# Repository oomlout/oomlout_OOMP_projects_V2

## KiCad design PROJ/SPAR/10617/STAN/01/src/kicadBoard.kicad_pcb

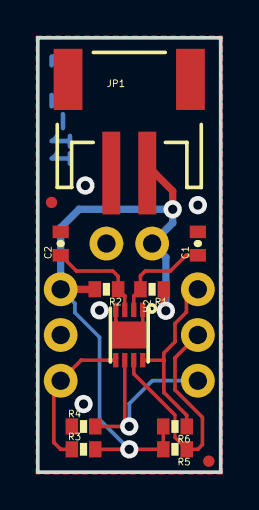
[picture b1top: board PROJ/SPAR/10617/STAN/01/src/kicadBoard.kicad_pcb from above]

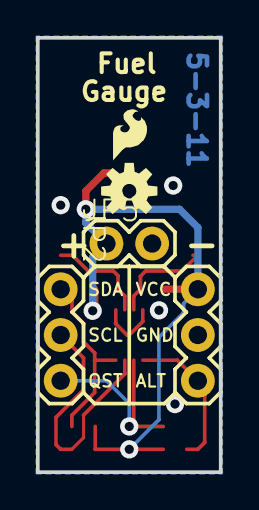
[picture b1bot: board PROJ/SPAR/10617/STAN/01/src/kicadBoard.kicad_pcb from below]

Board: 2 copper layers, 10.2 x 24.1 mm, 17 parts (5 on the bottom side), 8 nets.

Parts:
C1: 1uF; 0402-CAP
C2: 10nF; 0402-CAP
JP1: input; JST-2-SMD
JP2, JP4: 1X03
JP3: LOGO-SFESK; SFE-LOGO-FLAME
JP5: 1X02
JP6, JP7: FIDUCIAL1X2.5; FIDUCIAL-1X2.5
R1: 1k; 0402-RES
R2: 180; 0402-RES
R3, R4, R5, R6: 4.7k; 0402-RES
U2: MAX1704X; TDFN-8
U$1: OSHW-LOGOS; OSHW-LOGO-S

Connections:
ALT: JP4.3, R3.1, U2.5
GND: C1.2, C2.2, JP1.1, JP4.2, JP5.2, R4.1, U2.1, U2.4, U2.EP
unnamed: C1.1, R1.2, U2.2
QST: JP2.3, R4.2, U2.6
SCL: JP2.2, R5.1, U2.7
SDA: JP2.1, R6.1, U2.8
VCC: JP1.2, JP4.1, JP5.1, R1.1, R2.2, R3.2, R5.2, R6.2
VDD: C2.1, R2.1, U2.3

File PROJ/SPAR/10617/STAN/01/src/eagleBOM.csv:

"Part";"Value";"Device";"Package";"Description";"";
"C1";"1uF";"CAP0402-CAP";"0402-CAP";"Capacitor";"";
"C2";"10nF";"CAP0402-CAP";"0402-CAP";"Capacitor";"";
"JP1";"input";"M02-JST-2MM-SMT";"JST-2-SMD";"Header 2";"";
"JP2";"";"M03PTH";"1X03";"Header 3";"";
"JP3";"LOGO-SFESK";"LOGO-SFESK";"SFE-LOGO-FLAME";"Spark Fun Electronics PCB Logo";"";
"JP4";"";"M03PTH";"1X03";"Header 3";"";
"JP5";"";"M02PTH";"1X02";"Header 2";"";
"JP6";"FIDUCIAL1X2.5";"FIDUCIAL1X2.5";"FIDUCIAL-1X2.5";"Fiducial Alignment Points";"";
"JP7";"FIDUCIAL1X2.5";"FIDUCIAL1X2.5";"FIDUCIAL-1X2.5";"Fiducial Alignment Points";"";
"R1";"1k";"RESISTOR0402-RES";"0402-RES";"Resistor";"";
"R2";"180";"RESISTOR0402-RES";"0402-RES";"Resistor";"";
"R3";"4.7k";"RESISTOR0402-RES";"0402-RES";"Resistor";"";
"R4";"4.7k";"RESISTOR0402-RES";"0402-RES";"Resistor";"";
"R5";"4.7k";"RESISTOR0402-RES";"0402-RES";"Resistor";"";
"R6";"4.7k";"RESISTOR0402-RES";"0402-RES";"Resistor";"";
"U$1";"OSHW-LOGOS";"OSHW-LOGOS";"OSHW-LOGO-S";"Open Source Hardware Logo This logo indicates the piece of hardware it is found on incorporates a OSHW license and/or adheres to the definition of open source hardware found here: http://freedomdefined.org/OSHW";"";
"U2";"MAX1704X";"MAX1704X";"TDFN-8";"MAX17043/MAX17044: Battery Fuel Guage (43 is 1cell, 44 is 2cell)";"";

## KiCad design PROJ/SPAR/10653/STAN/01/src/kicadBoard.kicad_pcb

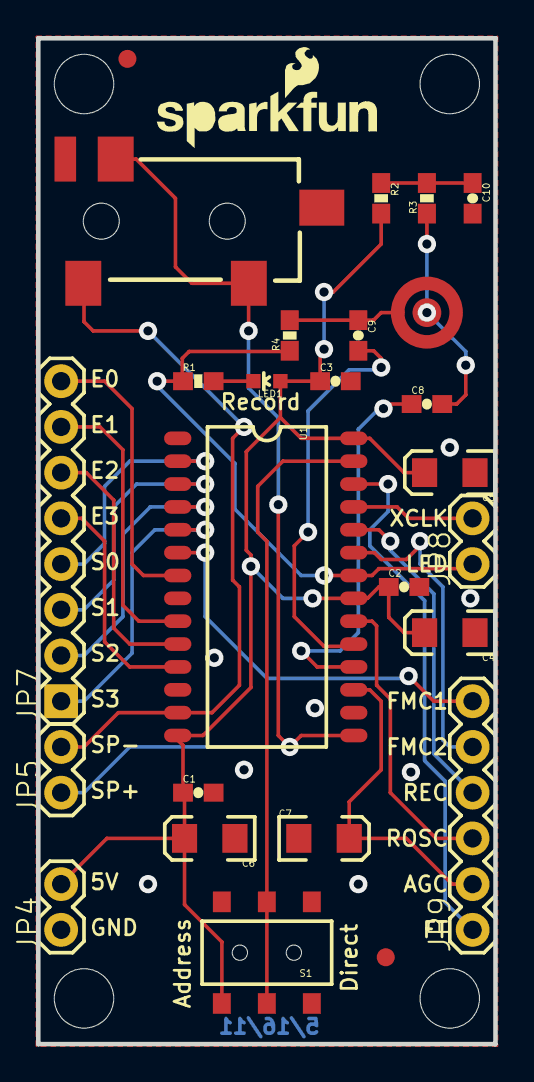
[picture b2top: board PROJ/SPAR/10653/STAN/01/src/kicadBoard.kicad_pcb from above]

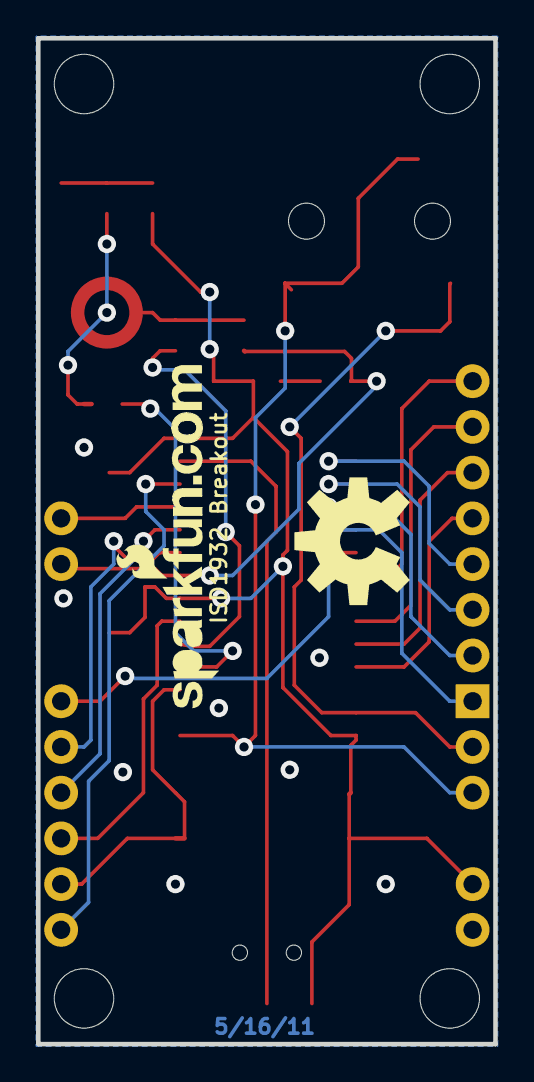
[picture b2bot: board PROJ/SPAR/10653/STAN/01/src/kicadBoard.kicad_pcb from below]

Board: 2 copper layers, 25.4 x 55.9 mm, 35 parts (2 on the bottom side), 27 nets.

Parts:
C1, C2, C3, C8, C9: 0.1uF; 0603-CAP
C4, C5, C6, C7: 10uF; EIA3216
C10: 4.7uF; 0603-CAP
JP1: LOGO-SFENEW; SFE-NEW-WEBLOGO
JP2, JP3: FIDUCIAL1X2; FIDUCIAL-1X2
JP4, JP5, JP8: 1X02
JP6, JP10, JP11, JP12: STAND-OFF
JP7: 1X08
JP9: 1X06
JP13: LOGO-SFENW2; SFE-NEW-WEB
LED1: Red; LED-0603
R1: 1k; 0603-RES
R2, R3, R4: 4.7k; 0603-RES
S1: AYZ0202
U1: ISD1900ISD1932; SO-28W
U2: MICELECTRET_SMD; MIC_ELECTRET_SMD
U3: AUDIO-JACK2SMD; AUDIO-JACK-3.5MM-SMD
U$10: CREATIVE_COMMONS
U$13: SFE-LOGO-FLAME
U$14: OSHW-LOGOL; OSHW-LOGO-L

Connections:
5V: C1.1, C2.1, C3.1, C4.A, C5.A, C6.A, JP4.2, LED1.A, R2.2, S1.3, U1.14, U1.21, U1.28
AGC: C7.A, JP9.2, U1.17
E0: JP7.8, U1.7
E1: JP7.7, U1.9
E2: JP7.6, U1.10
E3: JP7.5, U1.11
FMC1: JP9.6, U1.6
FMC2: JP9.5, U1.23
FT: JP9.1, U1.26
GND: C1.2, C2.2, C3.2, C4.C, C5.C, C6.C, C7.C, C10.2, JP4.1, S1.1, U1.1, U1.8, U1.12, U1.16
LED: JP8.1, R1.1, R4.1, U1.22
MIC+: C8.1, U1.18
MIC-: C9.2, U1.19
MODE: S1.2, U1.27
unnamed: LED1.C, R1.2
unnamed: C8.2, R3.1, U2.1
unnamed: C9.1, R4.2, U2.2
unnamed: C10.1, R2.1, R3.2
REC: JP9.4, U1.24
ROSC: JP9.3, U1.20
S0: JP7.4, U1.2
S1: JP7.3, U1.3
S2: JP7.2, U1.4
S3: JP7.1, U1.5
SP+: JP5.1, U1.15, U3.RING, U3.TIP
SP-: JP5.2, U1.13, U3.SLEEVE
XCLK: JP8.2, U1.25

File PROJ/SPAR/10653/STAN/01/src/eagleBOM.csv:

"Part";"Value";"Device";"Package";"Description";"";
"C1";"0.1uF";"CAP0603-CAP";"0603-CAP";"Capacitor";"";
"C2";"0.1uF";"CAP0603-CAP";"0603-CAP";"Capacitor";"";
"C3";"0.1uF";"CAP0603-CAP";"0603-CAP";"Capacitor";"";
"C4";"10uF";"CAP_POL1206";"EIA3216";"Capacitor Polarized";"";
"C5";"10uF";"CAP_POL1206";"EIA3216";"Capacitor Polarized";"";
"C6";"10uF";"CAP_POL1206";"EIA3216";"Capacitor Polarized";"";
"C7";"10uF";"CAP_POL1206";"EIA3216";"Capacitor Polarized";"";
"C8";"0.1uF";"CAP0603-CAP";"0603-CAP";"Capacitor";"";
"C9";"0.1uF";"CAP0603-CAP";"0603-CAP";"Capacitor";"";
"C10";"4.7uF";"CAP0603-CAP";"0603-CAP";"Capacitor";"";
"JP1";"LOGO-SFENEW";"LOGO-SFENEW";"SFE-NEW-WEBLOGO";"Spark Fun Electronics PCB Logo";"";
"JP2";"FIDUCIAL1X2";"FIDUCIAL1X2";"FIDUCIAL-1X2";"Fiducial Alignment Points";"";
"JP3";"FIDUCIAL1X2";"FIDUCIAL1X2";"FIDUCIAL-1X2";"Fiducial Alignment Points";"";
"JP4";"";"M02PTH";"1X02";"Header 2";"";
"JP5";"";"M02PTH";"1X02";"Header 2";"";
"JP6";"STAND-OFF";"STAND-OFF";"STAND-OFF";"Stand Off";"";
"JP7";"";"M08";"1X08";"Header 8";"";
"JP8";"";"M02PTH";"1X02";"Header 2";"";
"JP9";"";"M06SIP";"1X06";"Header 6";"";
"JP10";"STAND-OFF";"STAND-OFF";"STAND-OFF";"Stand Off";"";
"JP11";"STAND-OFF";"STAND-OFF";"STAND-OFF";"Stand Off";"";
"JP12";"STAND-OFF";"STAND-OFF";"STAND-OFF";"Stand Off";"";
"JP13";"LOGO-SFENW2";"LOGO-SFENW2";"SFE-NEW-WEB";"Spark Fun Electronics PCB Logo";"";
"LED1";"Red";"LED0603";"LED-0603";"LEDs";"";
"R1";"1k";"RESISTOR0603-RES";"0603-RES";"Resistor";"";
"R2";"4.7k";"RESISTOR0603-RES";"0603-RES";"Resistor";"";
"R3";"4.7k";"RESISTOR0603-RES";"0603-RES";"Resistor";"";
"R4";"4.7k";"RESISTOR0603-RES";"0603-RES";"Resistor";"";
"S1";"";"SWITCH-SPSTSMD";"AYZ0202";"SPST Switch";"";
"U$10";"CREATIVE_COMMONS";"CREATIVE_COMMONS";"CREATIVE_COMMONS";"";"";
"U$14";"OSHW-LOGOL";"OSHW-LOGOL";"OSHW-LOGO-L";"Open Source Hardware Logo This logo indicates the piece of hardware it is found on incorporates a OSHW license and/or adheres to the definition of open source hardware found here: http://freedomdefined.org/OSHW";"";
"U1";"ISD1900ISD1932";"ISD1900ISD1932";"SO-28W";"";"";
"U2";"MICELECTRET_SMD";"MICELECTRET_SMD";"MIC_ELECTRET_SMD";"Microphone";"";
"U3";"AUDIO-JACK2SMD";"AUDIO-JACK2SMD";"AUDIO-JACK-3.5MM-SMD";"";"";

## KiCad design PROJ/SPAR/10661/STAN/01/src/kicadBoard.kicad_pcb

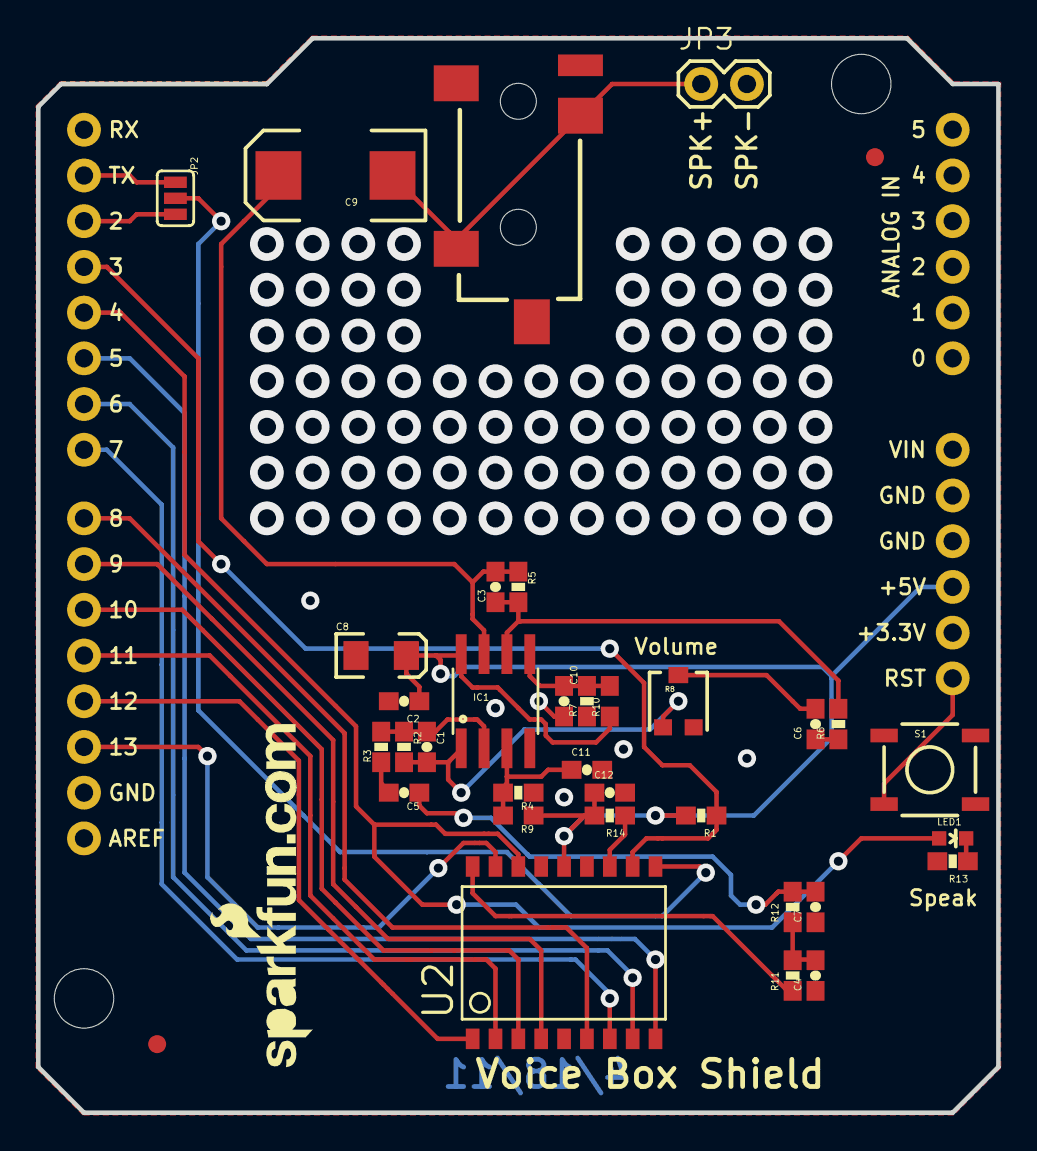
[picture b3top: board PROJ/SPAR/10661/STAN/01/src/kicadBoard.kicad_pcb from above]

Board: 2 copper layers, 53.3 x 59.7 mm, 37 parts (0 on the bottom side), 32 nets.

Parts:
C1, C3: 100pF; 0603-CAP
C2, C12: 0.1uF; 0603-CAP
C4, C7: 10 nF; 0603-CAP
C5, C6, C10, C11: 1uF; 0603-CAP
C8: 10uF; EIA3216
C9: 100 uF; EIA7343
IC1: OPAMP-DUALU; SO08
JP1: LOGO-SFENEW; SFE-NEW-WEBLOGO
JP2: JUMPER-32-3; SJ_3_PASTE2&3
JP3: Audio Header; 1X02
JP4, JP5: FIDUCIAL1X2; FIDUCIAL-1X2
JP6: 3.5mm SMD Audio Jack; AUDIO-JACK-3.5MM-SMD
LED1: Green; LED-0603
R1, R14: 10k; 0603-RES
R2, R5: 100K; 0603-RES
R3, R4, R6, R7: 10K; 0603-RES
R8: 10K Trimpot; TRIMPOT-3MM
R9, R10: 10K; 0603
R11, R12: 28k; 0603-RES
R13: 330; 0603-RES
S1: Reset Switch; TACTILE_SWITCH_SMD
U1: ARDUINO_SHIELDLABEL; DUEMILANOVE_SHIELD
U2: SPEAKJETSMD_WIDE; SO-18W

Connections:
AUDIO: C9.C, JP3.1, JP6.RING, JP6.TIP
D-TX: JP2.3, U1.D2
E0: U1.D5, U2.9
E1: U1.D6, U2.8
E2: U1.D7, U2.7
E3: U1.D8, U2.6
E4: U1.D9, U2.4
E5: U1.D10, U2.3
E6: U1.D11, U2.2
E7: U1.D12, U2.1
GND: C2.2, C4.1, C7.1, C8.C, C10.2, C11.2, C12.2, IC1.4, JP3.2, JP6.SLEEVE, R4.1, R7.1, R8.3, R13.2, S1.1, U1.GND@0, U1.GND@1, U1.GND@2, U2.5, U2.13
IN1: C5.2, R3.1
unnamed: JP2.2, U2.10
unnamed: C1.1, IC1.2, R2.1, R3.2
unnamed: C6.1, R6.1
unnamed: C6.2, R8.2
unnamed: C3.1, IC1.6, R5.2, R6.2
unnamed: C10.1, IC1.5, R7.2, R10.2
unnamed: C11.1, IC1.3, R4.2, R9.2
unnamed: C4.2, R11.2, R12.1
unnamed: C5.1, C7.2, R12.2
unnamed: LED1.C, R13.1
unnamed: R14.1, U2.12
OUT1: C1.2, IC1.1, R2.2, R8.1
RDY: U1.D13, U2.17
RESET: S1.3, U1.RES
RST: R1.1, U1.D3, U2.11
SPK: LED1.A, U1.D4, U2.16
SPK+: C3.2, C9.A, IC1.7, R5.1
TX: JP2.1, U1.TX
VCC: C2.1, C8.A, C12.1, IC1.8, R1.2, R9.1, R10.1, R14.2, U1.5V, U2.14
V_OUT: R11.1, U2.18

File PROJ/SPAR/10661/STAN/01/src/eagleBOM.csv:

"Part";"Value";"Device";"Package";"Description";"";
"C1";"100pF";"CAP0603-CAP";"0603-CAP";"Capacitor";"";
"C2";"0.1uF";"CAP0603-CAP";"0603-CAP";"Capacitor";"";
"C3";"100pF";"CAP0603-CAP";"0603-CAP";"Capacitor";"";
"C4";"10 nF";"CAP0603-CAP";"0603-CAP";"Capacitor";"";
"C5";"1uF";"CAP0603-CAP";"0603-CAP";"Capacitor";"";
"C6";"1uF";"CAP0603-CAP";"0603-CAP";"Capacitor";"";
"C7";"10 nF";"CAP0603-CAP";"0603-CAP";"Capacitor";"";
"C8";"10uF";"CAP_POL1206";"EIA3216";"Capacitor Polarized";"";
"C9";"100 uF";"CAP_POL7343";"EIA7343";"Capacitor Polarized";"";
"C10";"1uF";"CAP0603-CAP";"0603-CAP";"Capacitor";"";
"C11";"1uF";"CAP0603-CAP";"0603-CAP";"Capacitor";"";
"C12";"0.1uF";"CAP0603-CAP";"0603-CAP";"Capacitor";"";
"IC1";"OPAMP-DUALU";"OPAMP-DUALU";"SO08";"Operational Amplifier";"";
"JP1";"LOGO-SFENEW";"LOGO-SFENEW";"SFE-NEW-WEBLOGO";"Spark Fun Electronics PCB Logo";"";
"JP2";"JUMPER-32-3";"JUMPER-32-3";"SJ_3_PASTE2&3";"";"";
"JP3";"Audio Header";"M02PTH";"1X02";"Header 2";"";
"JP4";"FIDUCIAL1X2";"FIDUCIAL1X2";"FIDUCIAL-1X2";"Fiducial Alignment Points";"";
"JP5";"FIDUCIAL1X2";"FIDUCIAL1X2";"FIDUCIAL-1X2";"Fiducial Alignment Points";"";
"JP6";"3.5mm SMD Audio Jack";"AUDIO-JACKSMD2";"AUDIO-JACK-3.5MM-SMD";"3.5mm Audio Jack";"";
"LED1";"Green";"LED0603";"LED-0603";"LEDs";"";
"R1";"10k";"RESISTOR0603-RES";"0603-RES";"Resistor";"";
"R2";"100K";"RESISTOR0603-RES";"0603-RES";"Resistor";"";
"R3";"10K";"RESISTOR0603-RES";"0603-RES";"Resistor";"";
"R4";"10K";"RESISTOR0603-RES";"0603-RES";"Resistor";"";
"R5";"100K";"RESISTOR0603-RES";"0603-RES";"Resistor";"";
"R6";"10K";"RESISTOR0603-RES";"0603-RES";"Resistor";"";
"R7";"10K";"RESISTOR0603-RES";"0603-RES";"Resistor";"";
"R8";"10K Trimpot";"TRIMPOTSMD";"TRIMPOT-3MM";"";"";
"R9";"10K";"RESISTOR0603";"0603";"Resistor";"";
"R10";"10K";"RESISTOR0603";"0603";"Resistor";"";
"R11";"28k";"RESISTOR0603-RES";"0603-RES";"Resistor";"";
"R12";"28k";"RESISTOR0603-RES";"0603-RES";"Resistor";"";
"R13";"330";"RESISTOR0603-RES";"0603-RES";"Resistor";"";
"R14";"10k";"RESISTOR0603-RES";"0603-RES";"Resistor";"";
"S1";"Reset Switch";"SWITCH-MOMENTARY-2SMD";"TACTILE_SWITCH_SMD";"";"";
"U1";"ARDUINO_SHIELDLABEL";"ARDUINO_SHIELDLABEL";"DUEMILANOVE_SHIELD";"";"";
"U2";"SPEAKJETSMD_WIDE";"SPEAKJETSMD_WIDE";"SO-18W";"";"";

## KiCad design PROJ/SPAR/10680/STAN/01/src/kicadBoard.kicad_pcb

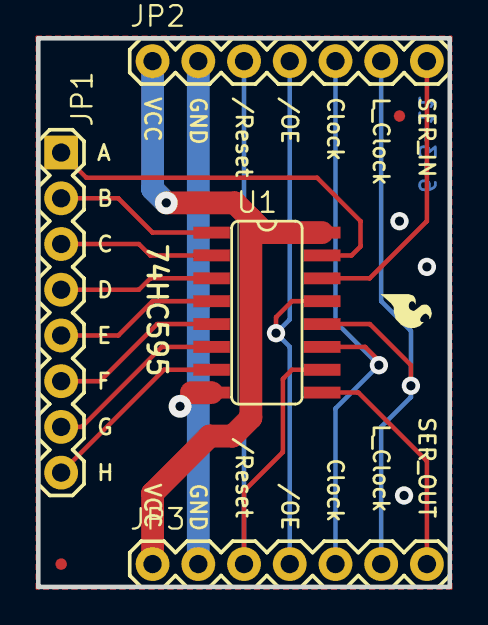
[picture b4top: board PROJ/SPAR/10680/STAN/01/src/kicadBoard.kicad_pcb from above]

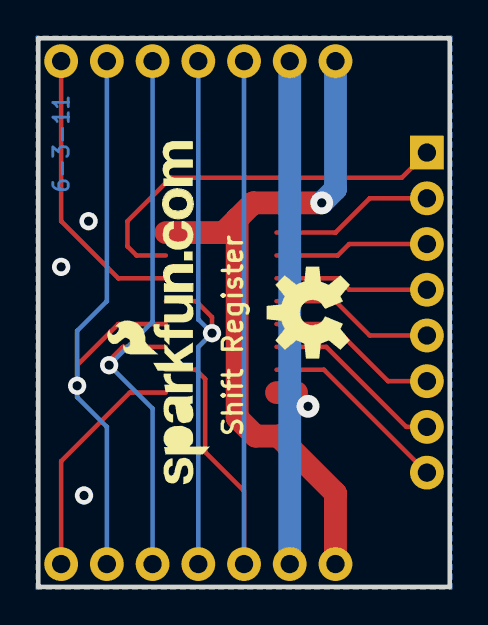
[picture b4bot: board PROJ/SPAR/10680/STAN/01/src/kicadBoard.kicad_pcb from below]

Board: 2 copper layers, 22.9 x 30.5 mm, 10 parts (2 on the bottom side), 16 nets.

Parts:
JP1: 1X08
JP2, JP3: 1X07
JP4: LOGO-SFENEW; SFE-NEW-WEBLOGO
JP5: LOGO-SFESK; SFE-LOGO-FLAME
JP6, JP7: FIDUCIAL1X2.5; FIDUCIAL-1X2.5
U1: 74LS595D; SO16
U$1: OSHW-LOGOM; OSHW-LOGO-M
U$2: CREATIVE_COMMONS

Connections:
/OUTPUT_ENABLE: JP2.4, JP3.4, U1.13
/RESET: JP2.3, JP3.3, U1.10
CLOCK: JP2.5, JP3.5, U1.11
GND: JP2.2, JP3.2, U1.8
LATCH_CLOCK: JP2.6, JP3.6, U1.12
unnamed: JP1.1, U1.15
unnamed: JP1.2, U1.1
unnamed: JP1.3, U1.2
unnamed: JP1.4, U1.3
unnamed: JP1.5, U1.4
unnamed: JP1.6, U1.5
unnamed: JP1.7, U1.6
unnamed: JP1.8, U1.7
SERIAL_IN: JP2.7, U1.14
SERIAL_OUT: JP3.7, U1.9
VCC: JP2.1, JP3.1, U1.16

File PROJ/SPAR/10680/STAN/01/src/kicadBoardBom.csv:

"Id";"Designator";"Package";"Quantity";"Designation";"Supplier and ref";
1;"JP1";"1X08";1;"";;;
2;"U$2";"CREATIVE_COMMONS";1;"CREATIVE_COMMONS";;;
3;"JP6,JP7";"FIDUCIAL-1X2.5";2;"FIDUCIAL1X2.5";;;
4;"JP2,JP3";"1X07";2;"";;;
5;"JP5";"SFE-LOGO-FLAME";1;"LOGO-SFESK";;;
6;"U1";"SO16";1;"74LS595D";;;
7;"U$1";"OSHW-LOGO-M";1;"OSHW-LOGOM";;;
8;"JP4";"SFE-NEW-WEBLOGO";1;"LOGO-SFENEW";;;

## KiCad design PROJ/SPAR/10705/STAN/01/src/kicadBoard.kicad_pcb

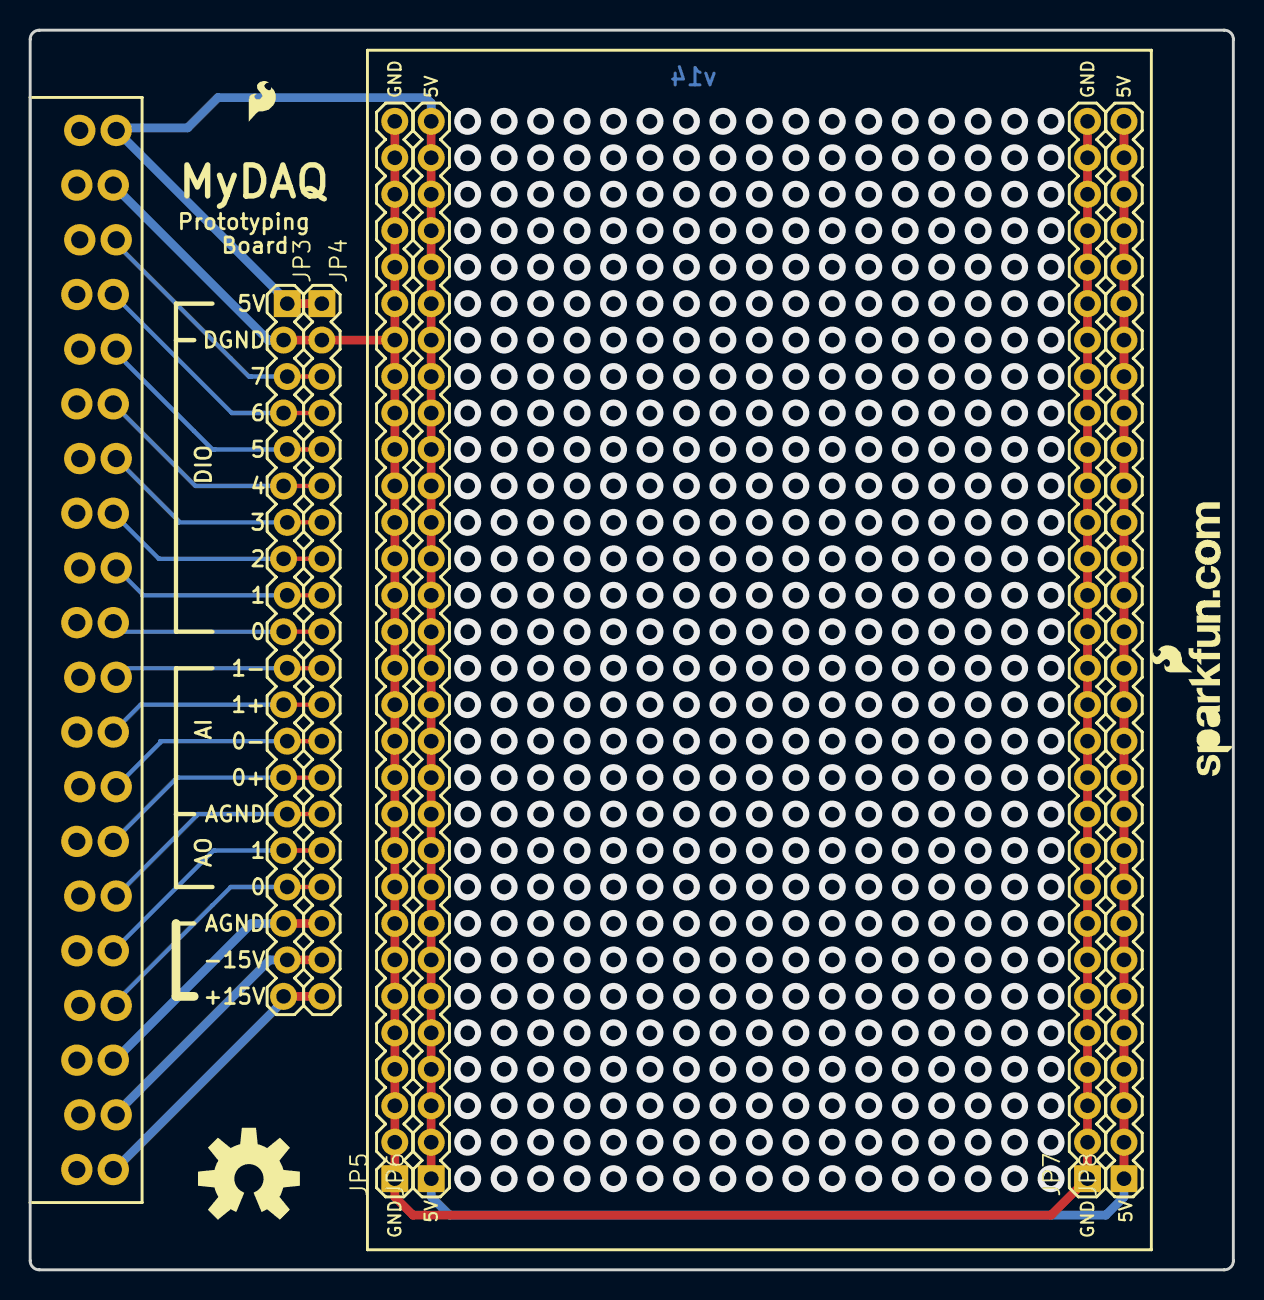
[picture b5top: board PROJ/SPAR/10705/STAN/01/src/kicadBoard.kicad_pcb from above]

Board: 2 copper layers, 83.8 x 86.4 mm, 13 parts (0 on the bottom side), 20 nets.

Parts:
FRAME2: FRAME-LETTER; CREATIVE_COMMONS
JP1: LOGO-SFENEW; SFE-NEW-WEBLOGO
JP2: MYDAQ; 3.81MM_TERMINAL_BLOCK_FEMALE_LOCKING
JP3: M20_LOCKINGFEMALE_LOCK.009; 1X20_LOCK
JP4: M20; 1X20
JP5, JP6, JP7, JP8: M30; 1X30
LOGO1: OSHW-LOGOL; OSHW-LOGO-L
LOGO2: LOGO-SFESK; SFE-LOGO-FLAME
U1: BREADBOARDCLEAR; BREADBOARD_CLEAR
U$3: REVISION

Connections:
5V: JP2.20, JP3.1, JP4.1, JP6.1, JP6.2, JP6.3, JP6.4, JP6.5, JP6.6, JP6.7, JP6.8, JP6.9, JP6.10, JP6.11, JP6.12, JP6.13, JP6.14, JP6.15, JP6.16, JP6.17, JP6.18, JP6.19, JP6.20, JP6.21, JP6.22, JP6.23, JP6.24, JP6.25, JP6.26, JP6.27, JP6.28, JP6.29, JP6.30, JP8.1, JP8.2, JP8.3, JP8.4, JP8.5, JP8.6, JP8.7, JP8.8, JP8.9, JP8.10, JP8.11, JP8.12, JP8.13, JP8.14, JP8.15, JP8.16, JP8.17, JP8.18, JP8.19, JP8.20, JP8.21, JP8.22, JP8.23, JP8.24, JP8.25, JP8.26, JP8.27, JP8.28, JP8.29, JP8.30
+15V: JP2.1, JP3.20, JP4.20
-15V: JP2.2, JP3.19, JP4.19
AGND_15V: JP2.3, JP3.18, JP4.18
AGND_IO: JP2.6, JP3.15, JP4.15
AI0+: JP2.7, JP3.14, JP4.14
AI0-: JP2.8, JP3.13, JP4.13
AI1+: JP2.9, JP3.12, JP4.12
AI1-: JP2.10, JP3.11, JP4.11
AO0: JP2.4, JP3.17, JP4.17
AO1: JP2.5, JP3.16, JP4.16
DIO0: JP2.11, JP3.10, JP4.10
DIO1: JP2.12, JP3.9, JP4.9
DIO2: JP2.13, JP3.8, JP4.8
DIO3: JP2.14, JP3.7, JP4.7
DIO4: JP2.15, JP3.6, JP4.6
DIO5: JP2.16, JP3.5, JP4.5
DIO6: JP2.17, JP3.4, JP4.4
DIO7: JP2.18, JP3.3, JP4.3
GND: JP2.19, JP3.2, JP4.2, JP5.1, JP5.2, JP5.3, JP5.4, JP5.5, JP5.6, JP5.7, JP5.8, JP5.9, JP5.10, JP5.11, JP5.12, JP5.13, JP5.14, JP5.15, JP5.16, JP5.17, JP5.18, JP5.19, JP5.20, JP5.21, JP5.22, JP5.23, JP5.24, JP5.25, JP5.26, JP5.27, JP5.28, JP5.29, JP5.30, JP7.1, JP7.2, JP7.3, JP7.4, JP7.5, JP7.6, JP7.7, JP7.8, JP7.9, JP7.10, JP7.11, JP7.12, JP7.13, JP7.14, JP7.15, JP7.16, JP7.17, JP7.18, JP7.19, JP7.20, JP7.21, JP7.22, JP7.23, JP7.24, JP7.25, JP7.26, JP7.27, JP7.28, JP7.29, JP7.30

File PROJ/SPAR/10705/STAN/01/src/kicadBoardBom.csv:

"Id";"Designator";"Package";"Quantity";"Designation";"Supplier and ref";
1;"LOGO2";"SFE-LOGO-FLAME";1;"LOGO-SFESK";;;
2;"JP6,JP5,JP7,JP8";"1X30";4;"M30";;;
3;"LOGO1";"OSHW-LOGO-L";1;"OSHW-LOGOL";;;
4;"FRAME2";"CREATIVE_COMMONS";1;"FRAME-LETTER";;;
5;"U$3";"REVISION";1;"REVISION";;;
6;"U1";"BREADBOARD_CLEAR";1;"BREADBOARDCLEAR";;;
7;"JP1";"SFE-NEW-WEBLOGO";1;"LOGO-SFENEW";;;
8;"JP2";"3.81MM_TERMINAL_BLOCK_FEMALE_LOCKING";1;"MYDAQ";;;
9;"JP3";"1X20_LOCK";1;"M20_LOCKINGFEMALE_LOCK.009";;;
10;"JP4";"1X20";1;"M20";;;

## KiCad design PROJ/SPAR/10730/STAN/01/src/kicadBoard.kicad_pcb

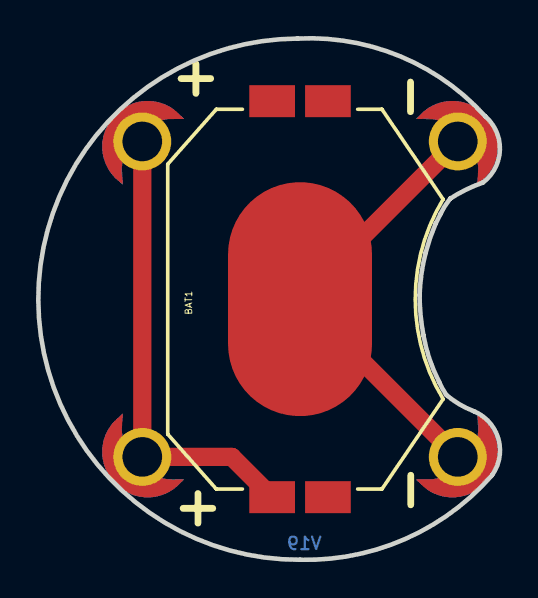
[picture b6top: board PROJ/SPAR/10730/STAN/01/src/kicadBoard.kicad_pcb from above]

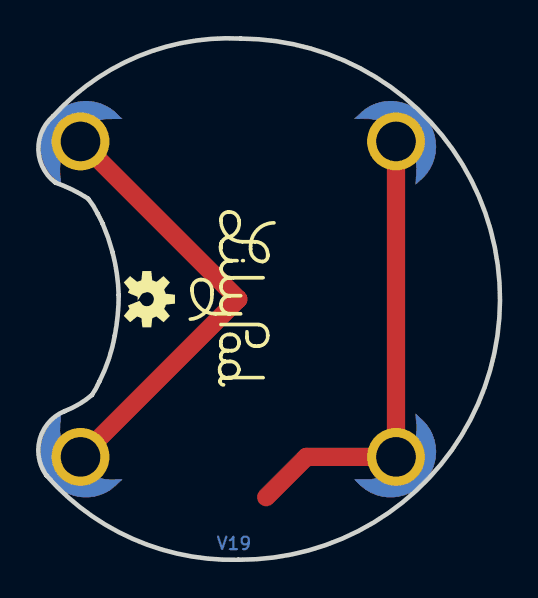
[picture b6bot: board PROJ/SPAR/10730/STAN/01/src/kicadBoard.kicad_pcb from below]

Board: 2 copper layers, 25.7 x 29.0 mm, 8 parts (2 on the bottom side), 2 nets.

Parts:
BAT1: 20mm coincell; BATTCON_20MM_4LEGS_OVERPASTE
U$1, U$2, U$3, U$4: SEWTAP6; PETAL-SMALL-2SIDE
U$5: LOGO-LPLP; LOGO-LILYPAD
U$6: CREATIVE_COMMONS
U$7: OSHW-LOGOS; OSHW-LOGO-S

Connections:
+: BAT1.1, U$2.1, U$4.1
-: BAT1.2, U$1.1, U$3.1

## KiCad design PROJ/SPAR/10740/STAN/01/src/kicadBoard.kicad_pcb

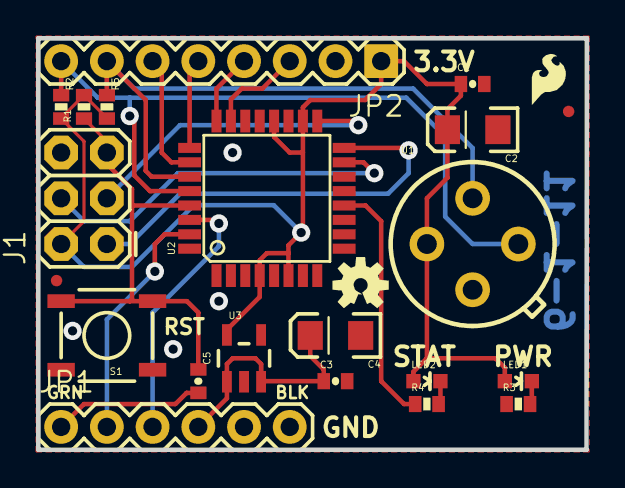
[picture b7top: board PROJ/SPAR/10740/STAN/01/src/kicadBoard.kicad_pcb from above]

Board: 2 copper layers, 30.5 x 22.9 mm, 23 parts (0 on the bottom side), 19 nets.

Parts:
C1, C3, C5: 0.1uF; 0402-CAP
C2, C4: 10uF; EIA3216
J1: AVR_SPI_PRG_6PTH; 2X3
JP1: FTDI; 1X06
JP2: PORTC; 1X08
JP3, JP5: FIDUCIAL1X2.5; FIDUCIAL-1X2.5
JP4: LOGO-SFESK; SFE-LOGO-FLAME
LED1: red; LED-0603
LED2: green; LED-0603
R1, R2, R5: 10k; 0402-RES
R3, R4: 330; 0402-RES
S1: Reset; TACTILE_SWITCH_SMD
U1: MLX90614_; TO-39
U2: ATMEGA328; TQFP32-08
U3: 3.3V_REG; SOT23-5
U$1: OSHW-LOGOS; OSHW-LOGO-S

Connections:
3.3V: C1.1, C2.A, J1.2, JP2.1, LED1.A, LED2.A, R1.2, R2.2, R5.2, U1.3, U2.4, U2.6, U2.18, U2.20, U3.5
DTR: C5.2, JP1.1
GND: C1.2, C2.C, C3.2, C4.C, J1.6, JP1.5, JP1.6, JP2.2, R3.1, S1.1, S1.2, U1.4, U2.3, U2.5, U2.21, U3.2
LED: R4.1, U2.12
MISO: J1.1, U2.16
MOSI: J1.4, U2.15
unnamed: LED1.C, R3.2
unnamed: LED2.C, R4.2
PC0: JP2.3, U2.23
PC1: JP2.4, U2.24
PC2: JP2.5, U2.25
PC3: JP2.6, U2.26
RST: C5.1, J1.5, R1.1, S1.3, S1.4, U2.29
RX: JP1.2, U2.31
SCK: J1.3, U2.17
SCL: JP2.8, R2.1, U1.1, U2.28
SDA: JP2.7, R5.1, U1.2, U2.27
TX: JP1.3, U2.30
VCC: C3.1, C4.A, JP1.4, U3.1, U3.3

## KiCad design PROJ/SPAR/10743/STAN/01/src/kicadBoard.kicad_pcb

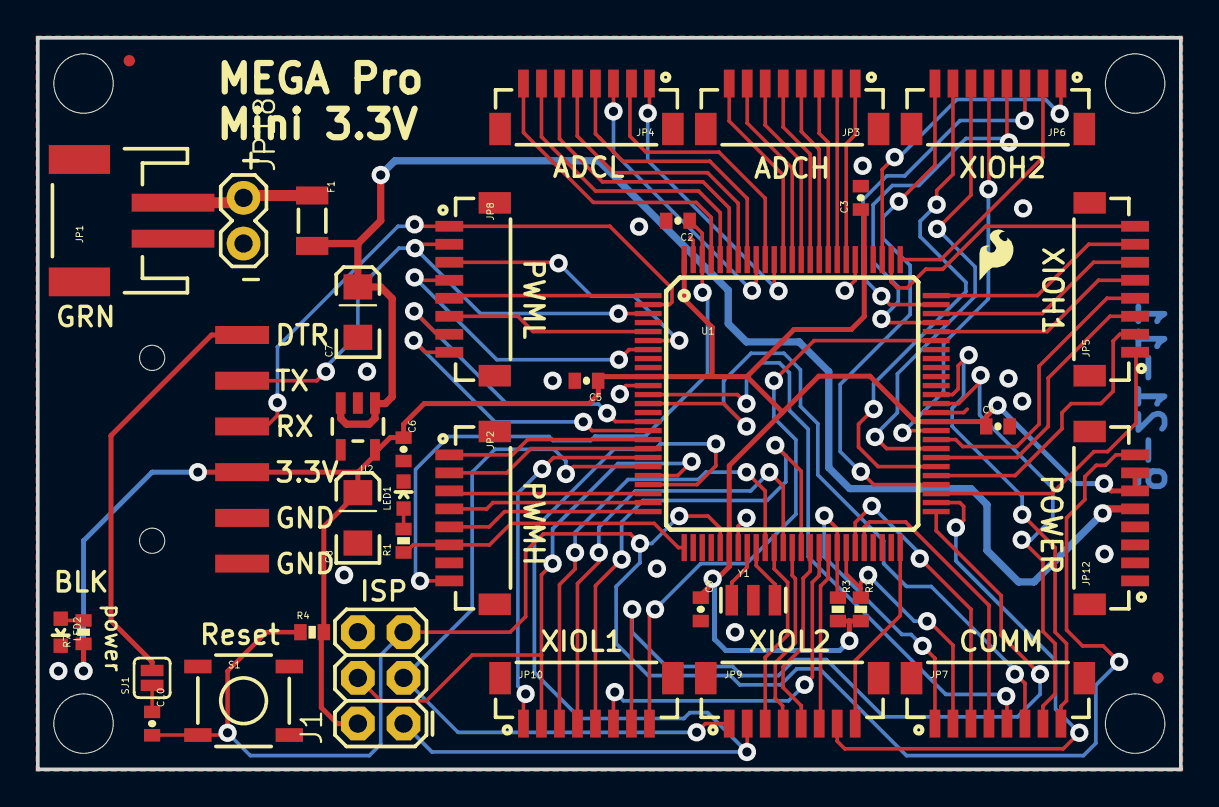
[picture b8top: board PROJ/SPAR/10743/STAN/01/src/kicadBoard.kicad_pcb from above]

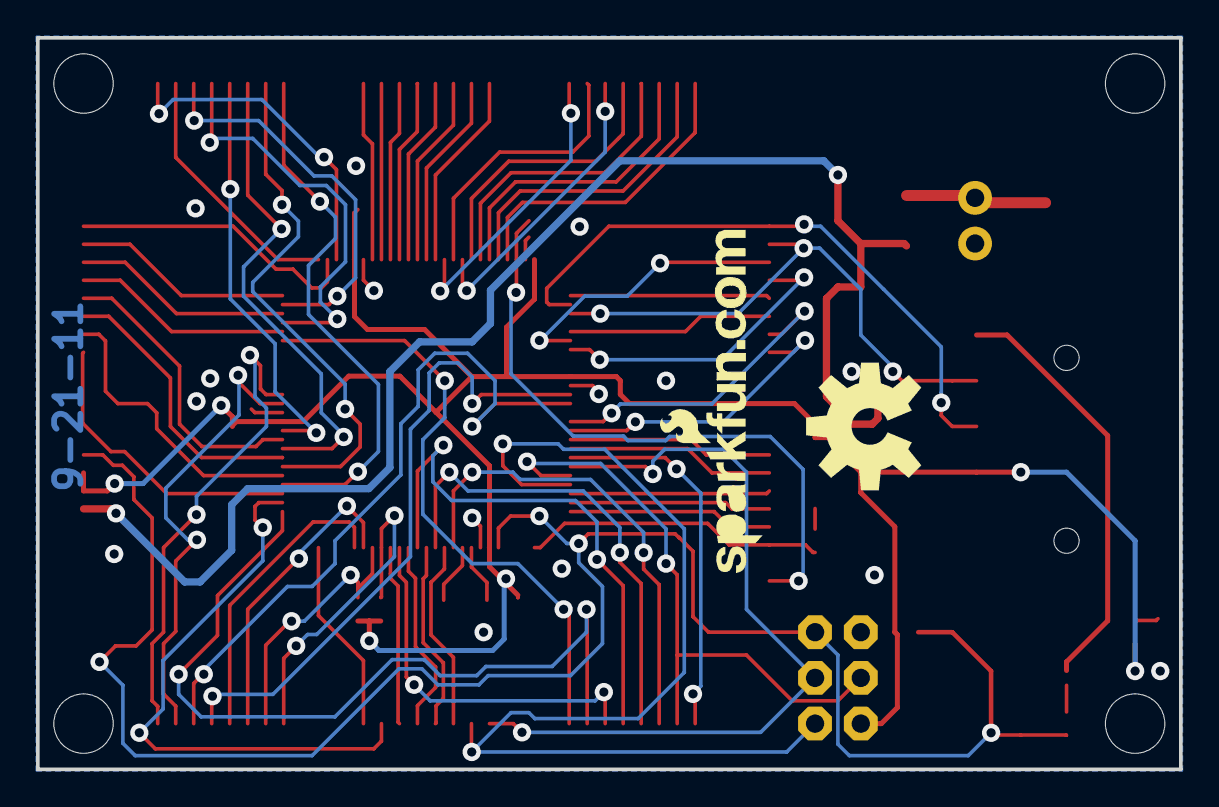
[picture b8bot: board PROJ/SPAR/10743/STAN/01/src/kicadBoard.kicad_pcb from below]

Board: 2 copper layers, 63.5 x 40.6 mm, 45 parts (2 on the bottom side), 82 nets.

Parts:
C2, C3, C4, C5, C6, C9, C10: 0.1uF; 0402-CAP
C7, C8: 10uF; EIA3216
F1: PTCSMD; PTC-1206
J1: ISP; 2X3
JP1: LiPo; JST-2-SMD
JP2: PWMH; BM08B-SRSS-TB
JP3: ADCH; BM08B-SRSS-TB
JP4: ADCL; BM08B-SRSS-TB
JP5: XIOH1; BM08B-SRSS-TB
JP6: XIOH2; BM08B-SRSS-TB
JP7: COMM; BM08B-SRSS-TB
JP8: PWML; BM08B-SRSS-TB
JP9: XIOL2; BM08B-SRSS-TB
JP10: XIOL1; BM08B-SRSS-TB
JP11, JP13, JP14, JP15: STAND-OFF
JP12: POWER; BM08B-SRSS-TB
JP16: LOGO-SFENEW; SFE-NEW-WEBLOGO
JP17: LOGO-SFESK; SFE-LOGO-FLAME
JP18: RAW; 1X02
JP19: FTDI; 1X06-SMD
JP20, JP21: FIDUCIAL1X2.5; FIDUCIAL-1X2.5
LED1: yellow; LED-0603
LED2: green; LED-0603
R1, R7: 1k; 0402-RES
R2, R3, R4: 10k; 0402-RES
S1: SWITCH-MOMENTARY-2SMD; TACTILE_SWITCH_SMD
SJ1: RESET-EN; SJ_2S
U1: ATMEGA2560AU; TQFP100
U2: V_REG_3.3V; SOT23-5
U$9: OSHW-LOGOL; OSHW-LOGO-L
Y1: RESONATORSMD; RESONATOR-SMD

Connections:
3.3V: C3.1, C4.1, C5.1, C6.1, C8.A, C9.1, J1.2, JP12.6, JP12.7, JP19.4, R2.2, R3.2, R4.2, R7.1, U1.10, U1.31, U1.61, U1.80, U1.100, U2.5
ADC0: JP4.8, U1.97
ADC1: JP4.7, U1.96
ADC2: JP4.6, U1.95
ADC3: JP4.5, U1.94
ADC4: JP4.4, U1.93
ADC5: JP4.3, U1.92
ADC6: JP4.2, U1.91
ADC7: JP4.1, U1.90
ADC8: JP3.8, U1.89
ADC9: JP3.7, U1.88
ADC10: JP3.6, U1.87
ADC11: JP3.5, U1.86
ADC12: JP3.4, U1.85
ADC13: JP3.3, U1.84
ADC14: JP3.2, U1.83
ADC15: JP3.1, U1.82
AREF: C2.1, JP2.8, U1.98
DTR: JP19.1, SJ1.2
GND: C2.2, C3.2, C4.2, C5.2, C6.2, C7.C, C8.C, C9.2, J1.6, JP1.1, JP2.7, JP12.1, JP12.2, JP12.3, JP12.4, JP18.2, JP19.5, JP19.6, LED1.C, LED2.C, S1.1, U1.11, U1.32, U1.62, U1.81, U1.99, U2.2, Y1.2
unnamed: F1.1, JP1.2, JP18.1
unnamed: LED1.A, R1.2
unnamed: LED2.A, R7.2
unnamed: U1.34, Y1.3
unnamed: U1.33, Y1.1
unnamed: C10.1, SJ1.1
PA0: JP6.1, U1.78
PA1: JP5.8, U1.77
PA2: JP6.2, U1.76
PA3: JP5.7, U1.75
PA4: JP6.3, U1.74
PA5: JP5.6, U1.73
PA6: JP6.4, U1.72
PA7: JP5.5, U1.71
PB0: JP10.1, U1.19
PB1: J1.3, JP9.1, U1.20
PB2: J1.4, JP10.2, U1.21
PB3: J1.1, JP9.2, U1.22
PB4: JP2.3, U1.23
PB5: JP2.4, U1.24
PB6: JP2.5, U1.25
PB7: JP2.6, R1.1, U1.26
PC0: JP5.1, U1.53
PC1: JP6.8, U1.54
PC2: JP5.2, U1.55
PC3: JP6.7, U1.56
PC4: JP5.3, U1.57
PC5: JP6.6, U1.58
PC6: JP5.4, U1.59
PC7: JP6.5, U1.60
PD7: JP9.8, U1.50
PE0: JP8.1, JP19.3, U1.2
PE1: JP8.2, JP19.2, U1.3
PE3: JP8.6, U1.5
PE4: JP8.3, U1.6
PE5: JP8.4, U1.7
PG0: JP10.7, U1.51
PG1: JP9.7, U1.52
PG2: JP10.8, U1.70
PG5: JP8.5, U1.1
PH3: JP8.7, U1.15
PH4: JP8.8, U1.16
PH5: JP2.1, U1.17
PH6: JP2.2, U1.18
PL0: JP10.3, U1.35
PL1: JP9.3, U1.36
PL2: JP10.4, U1.37
PL3: JP9.4, U1.38
PL4: JP10.5, U1.39
PL5: JP9.5, U1.40
PL6: JP10.6, U1.41
PL7: JP9.6, U1.42
RESET: C10.2, J1.5, JP12.8, R4.1, S1.3, U1.30
RXD1: JP7.3, U1.45
RXD2: JP7.5, U1.12
RXD3: JP7.7, U1.63
SCL: JP7.1, R3.1, U1.43
SDA: JP7.2, R2.1, U1.44
TXD1: JP7.4, U1.46
TXD2: JP7.6, U1.13
TXD3: JP7.8, U1.64
VIN: C7.A, F1.2, JP12.5, U2.1, U2.3

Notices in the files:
parts and their libraries:
HTTP://CREATIVECOMMONS.ORG/LICENSES/BY-SA/3.0
RELEASED UNDER THE CREATIVE COMMONS ATTRIBUTION SHARE-ALIKE 3.0 LICENSE
